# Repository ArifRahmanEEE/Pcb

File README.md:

# Pcb
PCB Design and schematic of Boost Converter on kicad

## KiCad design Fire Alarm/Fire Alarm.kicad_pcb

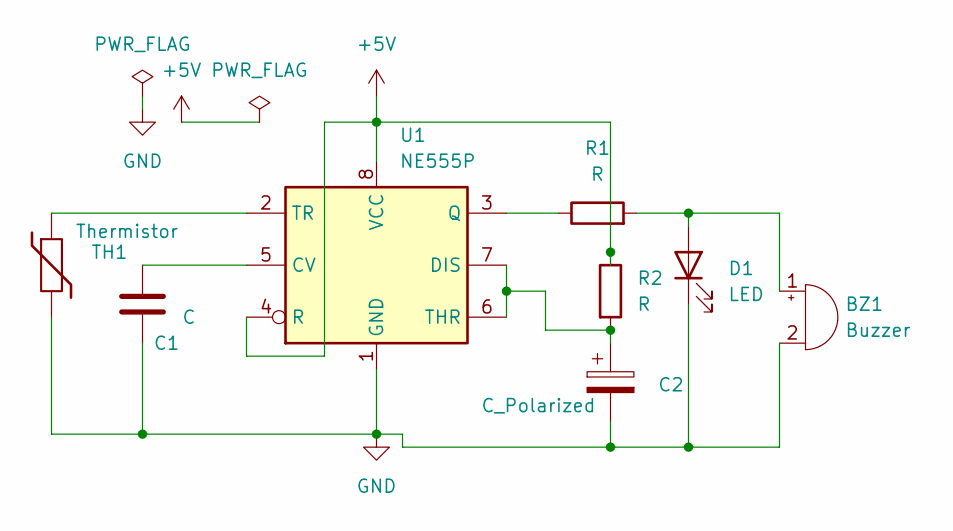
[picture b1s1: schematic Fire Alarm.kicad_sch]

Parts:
BZ1: Buzzer; MagneticBuzzer_Kingstate_KCG0601
C1: C; C_Disc_D3.4mm_W2.1mm_P2.50mm
C2: C_Polarized; CP_Radial_D5.0mm_P2.50mm
D1: LED; LED_D3.0mm
R1, R2: R; R_Axial_DIN0204_L3.6mm_D1.6mm_P7.62mm_Horizontal
TH1: Thermistor; TerminalBlock_bornier-2_P5.08mm
U1: NE555P; DIP-8_W7.62mm_LongPads

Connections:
+5V: R2.1, U1.4 (R), U1.8 (VCC)
GND: BZ1.2 (-), C1.2, C2.2, D1.1 (K), TH1.2, U1.1 (GND)
unnamed: BZ1.1 (+), D1.2 (A), R1.2
unnamed: C1.1, U1.5 (CV)
unnamed: C2.1, R2.2, U1.6 (THR), U1.7 (DIS)
unnamed: R1.1, U1.3 (Q)
unnamed: TH1.1, U1.2 (TR)

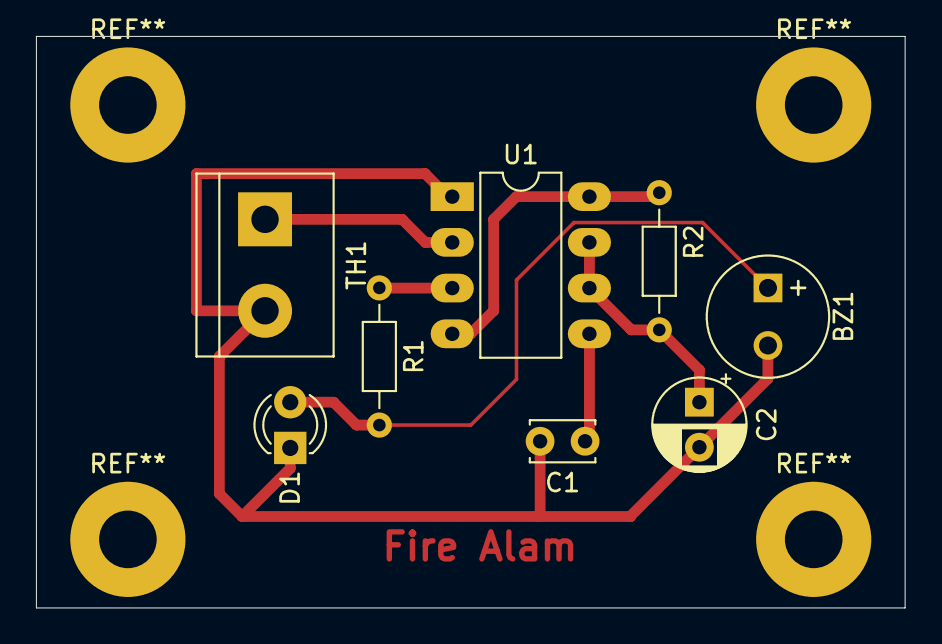
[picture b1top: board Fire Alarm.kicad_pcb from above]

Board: 2 copper layers, 48.3 x 31.8 mm, 8 parts (0 on the bottom side), 7 nets.
